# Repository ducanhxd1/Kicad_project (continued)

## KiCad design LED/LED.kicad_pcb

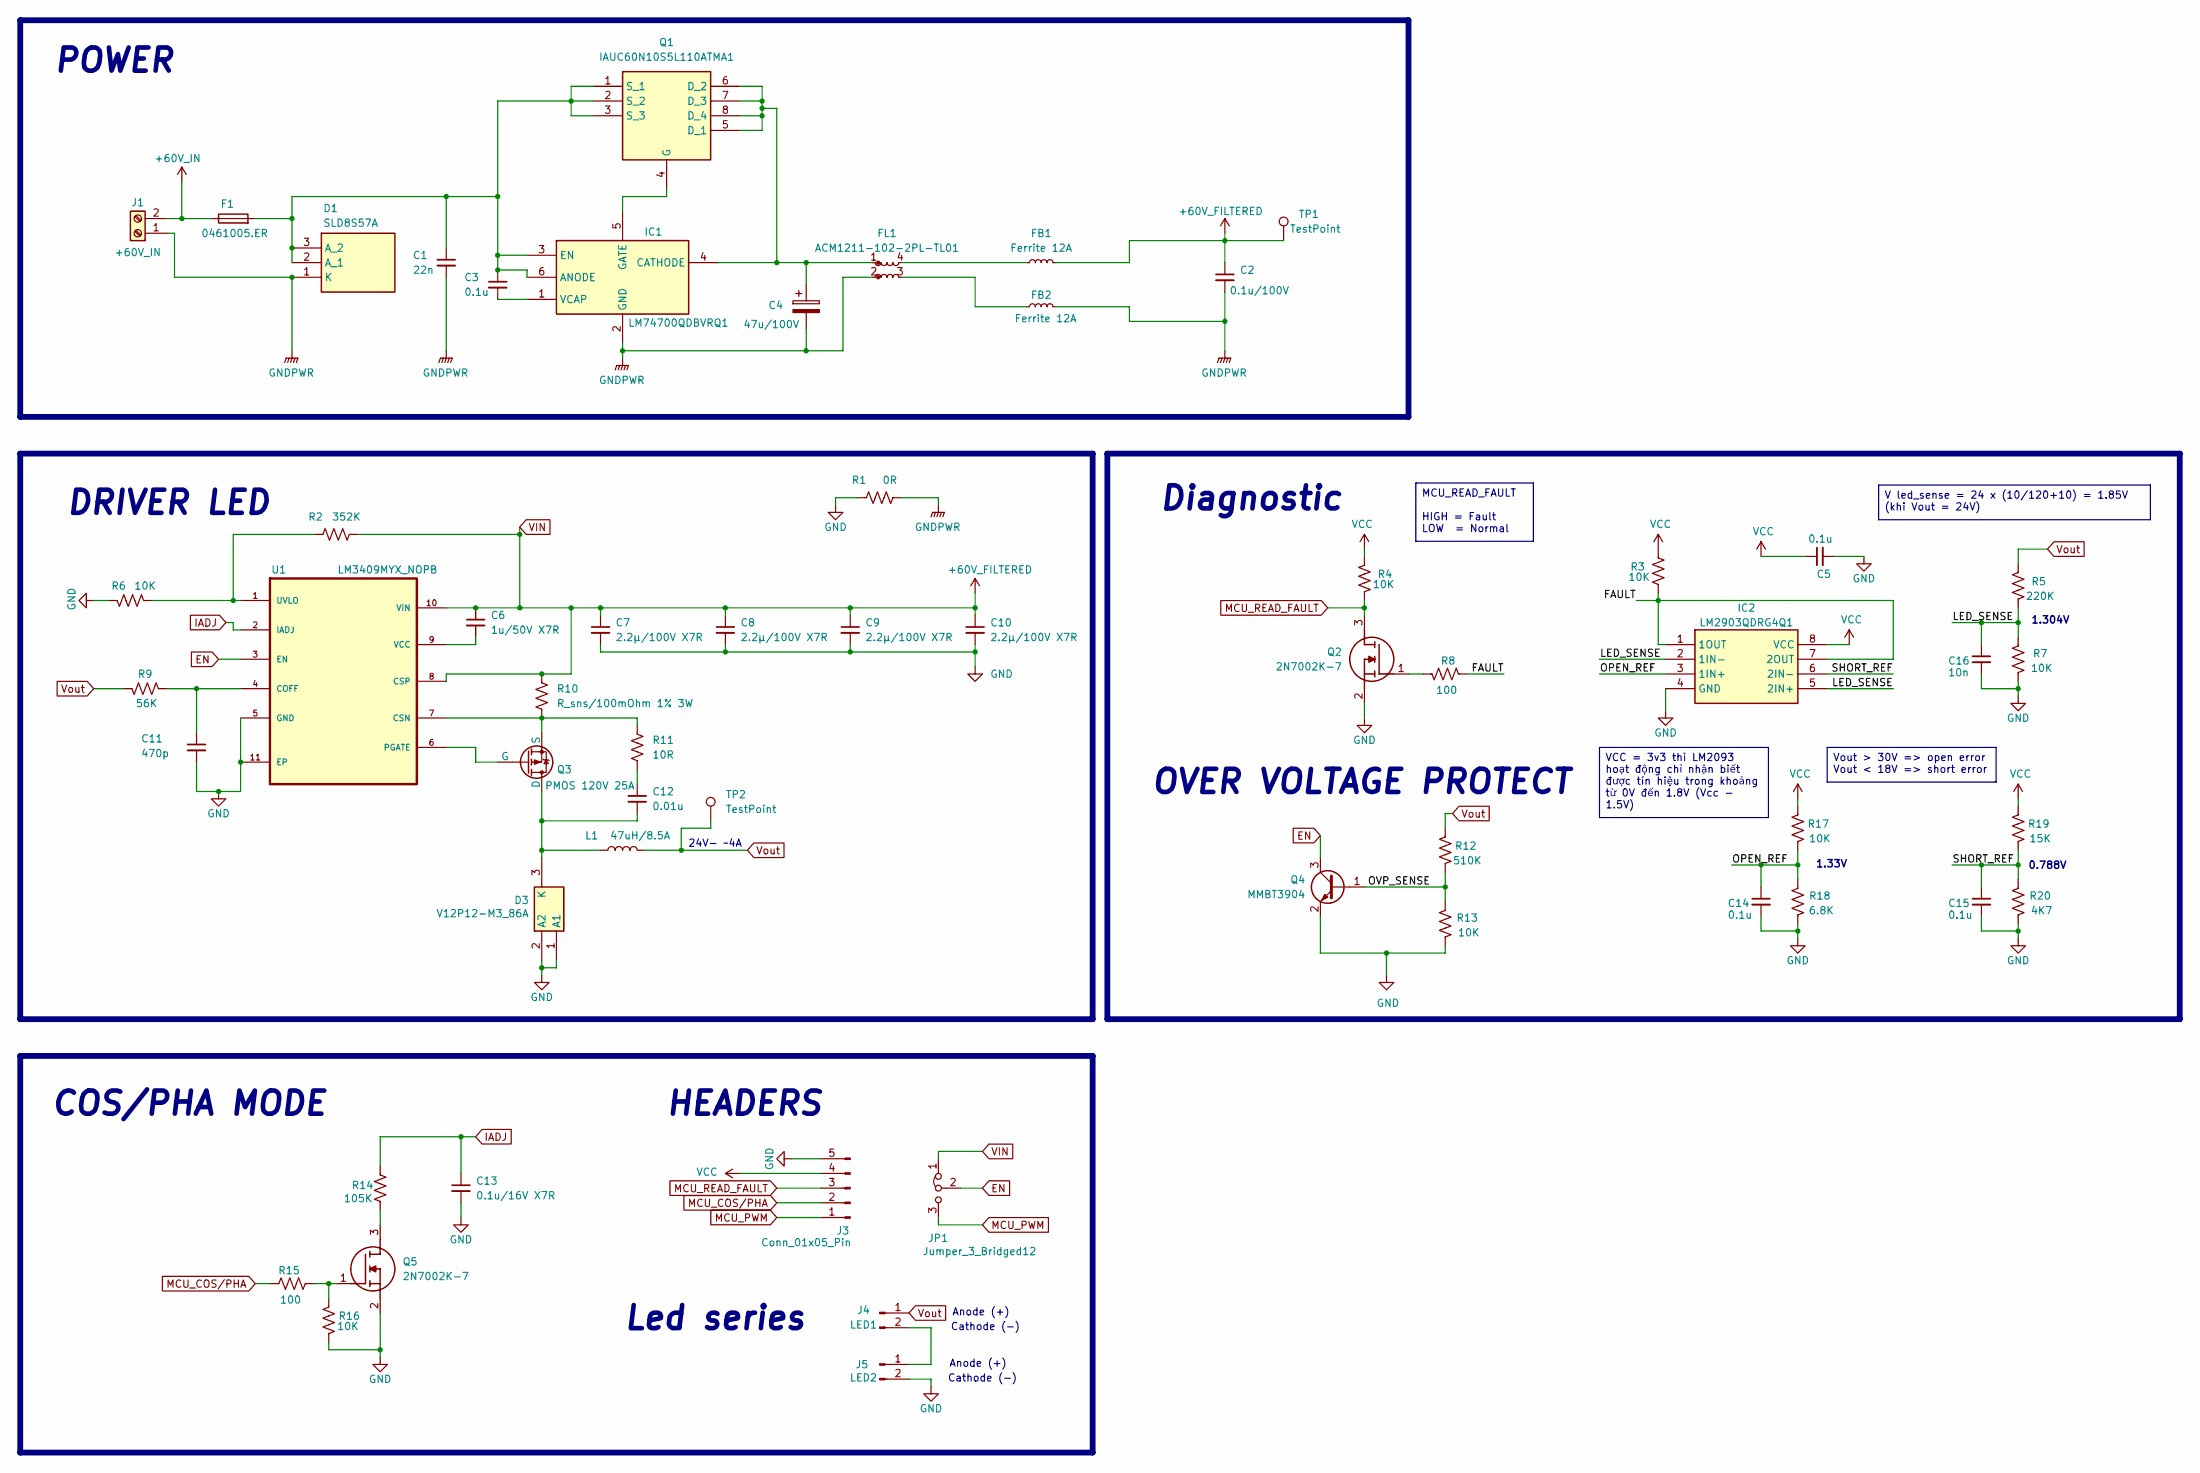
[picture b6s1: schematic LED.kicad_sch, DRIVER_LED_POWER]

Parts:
C1: 22n; C_0603_1608Metric_Pad1.08x0.95mm_HandSolder
C2: 0.1u/100V; C_0603_1608Metric_Pad1.08x0.95mm_HandSolder
C3, C5, C14, C15: 0.1u; C_0603_1608Metric_Pad1.08x0.95mm_HandSolder
C4: 47u/100V; CP_Elec_10x10.5
C6: 1u/50V X7R; C_0603_1608Metric_Pad1.08x0.95mm_HandSolder
C7, C8, C9, C10: 2.2µ/100V X7R; C_0603_1608Metric_Pad1.08x0.95mm_HandSolder
C11: 470p; C_0603_1608Metric_Pad1.08x0.95mm_HandSolder
C12: 0.01u; C_0603_1608Metric_Pad1.08x0.95mm_HandSolder
C13: 0.1u/16V X7R; C_0603_1608Metric_Pad1.08x0.95mm_HandSolder
C16: 10n; C_0603_1608Metric_Pad1.08x0.95mm_HandSolder
D1: SLD8S57A; Mouser Part Number 576-SLD8S57A
D3: V12P12-M3_86A; V12P12M386A; Manufacturer_Part_Number V12P12-M3/86A
F1: 0461005.ER; FUSC10131X312N
FB1, FB2: Ferrite 12A; BEADC3216X110N
FL1: ACM1211-102-2PL-TL01; ACM1211
IC1: LM74700QDBVRQ1; SOT95P280X145-6N; Mouser Part Number 595-LM74700QDBVRQ1
IC2: LM2903QDRG4Q1; SOIC127P600X175-8N; Mouser Part Number 595-LM2903QDRG4Q1
J1: +60V_IN; PinHeader_1x02_P2.54mm_Vertical
J3: Conn_01x05_Pin; JST_XH_B5B-XH-A_1x05_P2.50mm_Vertical
J4: LED1; JST_XH_B2B-XH-A_1x02_P2.50mm_Vertical
J5: LED2; JST_XH_B2B-XH-A_1x02_P2.50mm_Vertical
JP1: Jumper_3_Bridged12; PinHeader_1x03_P1.27mm_Vertical
L1: 47uH/8.5A; XAL1010
Q1: IAUC60N10S5L110ATMA1; Manufacturer_Part_Number IAUC60N10S5L110ATMA1
Q2, Q5: 2N7002K-7; SOT96P240X115-3N; Mouser Part Number 621-2N7002K-7
Q3: PMOS 120V 25A; SQD50P0825L_GE3
Q4: MMBT3904; SOT-23
R1: 0R; R_1206_3216Metric_Pad1.30x1.75mm_HandSolder
R2: 352K; R_0603_1608Metric_Pad0.98x0.95mm_HandSolder
R3, R4, R6, R7, R13, R16, R17: 10K; R_0603_1608Metric_Pad0.98x0.95mm_HandSolder
R5: 220K; R_0603_1608Metric_Pad0.98x0.95mm_HandSolder
R8, R15: 100; R_0603_1608Metric_Pad0.98x0.95mm_HandSolder
R9: 56K; R_0603_1608Metric_Pad0.98x0.95mm_HandSolder
R10: R_sns/100mOhm 1% 3W; R_2512_6332Metric_Pad1.40x3.35mm_HandSolder
R11: 10R; R_0603_1608Metric_Pad0.98x0.95mm_HandSolder
R12: 510K; R_0603_1608Metric_Pad0.98x0.95mm_HandSolder
R14: 105K; R_0603_1608Metric_Pad0.98x0.95mm_HandSolder
R18: 6.8K; R_0603_1608Metric_Pad0.98x0.95mm_HandSolder
R19: 15K; R_0603_1608Metric_Pad0.98x0.95mm_HandSolder
R20: 4K7; R_0603_1608Metric_Pad0.98x0.95mm_HandSolder
TP1, TP2: TestPoint; TestPoint_Pad_D1.0mm
U1: LM3409MYX_NOPB; IC_XTR111AIDGQR

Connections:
+60V_IN: F1.1, J1.2
/CS-: Q3.3 (S), R10.2, R11.1, U1.7 (CSN)
/FAULT: IC2.1 (1OUT), IC2.7 (2OUT), R3.1, R8.2
/LED_SENSE: C16.1, IC2.2 (1IN-), IC2.5 (2IN+), R5.1, R7.2
/OPEN_REF: C14.1, IC2.3 (1IN+), R17.1, R18.2
/OVP_SENSE: Q4.1 (B), R12.1, R13.2
/SHORT_REF: C15.1, IC2.6 (2IN-), R19.1, R20.2
EN: JP1.2 (C), Q4.3 (C), U1.3 (EN)
GND: C5.2, C7.2, C8.2, C9.2, C10.2, C11.2, C13.2, C14.2, C15.2, C16.2, D3.1 (A1), D3.2 (A2), IC2.4 (GND), J3.5, J5.2, Q2.2 (S), Q4.2 (E), Q5.2 (S), R1.2, R6.2, R7.1, R13.1, R16.1, R18.1, R20.1, U1.5 (GND), U1.11 (EP), U1.12, U1.13, U1.14, U1.15, U1.16
GNDPWR: C1.2, C2.2, C4.2, D1.1 (K), FB2.2, FL1.2, IC1.2 (GND), J1.1, R1.1
IADJ: C13.1, R14.1, U1.2 (IADJ)
MCU_COS/PHA: J3.2, R15.2
MCU_PWM: J3.1, JP1.3 (B)
MCU_READ_FAULT: J3.3, Q2.3 (D), R4.1
unnamed: C12.1, R11.2
unnamed: C1.1, C3.1, D1.2 (A_1), D1.3 (A_2), F1.2, IC1.3 (EN), IC1.6 (ANODE), Q1.1 (S_1), Q1.2 (S_2), Q1.3 (S_3), Q1.10
unnamed: C12.2, D3.3 (K), L1.1, Q3.1 (D)
unnamed: FB1.1, FL1.4
unnamed: FB2.1, FL1.3
unnamed: C4.1, FL1.1, IC1.4 (CATHODE), Q1.5 (D_1), Q1.6 (D_2), Q1.7 (D_3), Q1.8 (D_4), Q1.9
unnamed: IC1.5 (GATE), Q1.4 (G)
unnamed: C3.2, IC1.1 (VCAP)
unnamed: J4.2, J5.1
unnamed: Q2.1 (G), R8.1
unnamed: Q3.2 (G), U1.6 (PGATE)
unnamed: Q5.3 (D), R14.2
unnamed: Q5.1 (G), R15.1, R16.2
unnamed: C11.1, R9.1, U1.4 (COFF)
unnamed: R2.2, R6.1, U1.1 (UVLO)
unnamed: C6.2, U1.9 (VCC)
VCC: C5.1, IC2.8 (VCC), J3.4, R3.2, R4.2, R17.2, R19.2
VIN: C2.1, C6.1, C7.1, C8.1, C9.1, C10.1, FB1.2, JP1.1 (A), R2.1, R10.1, TP1.1 (1_1), U1.8 (CSP), U1.10 (VIN)
Vout: J4.1, L1.2, R5.2, R9.2, R12.2, TP2.1 (1_1)

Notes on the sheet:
Led series
OVER VOLTAGE PROTECT
Anode (+)
0.788V
Cathode (-)
24V- ~4A
HEADERS
Diagnostic
POWER
1.304V
DRIVER LED
COS/PHA MODE
1.33V
MCU_READ_FAULT HIGH = Fault LOW = Normal
V led_sense = 24 x (10/120+10) = 1.85V (khi Vout = 24V)
VCC = 3v3 thì LM2093 hoạt động chỉ nhận biết được tín hiệu trong khoảng từ 0V đến 1.8V (Vcc - 1.5V)
Vout > 30V => open error Vout < 18V => short error

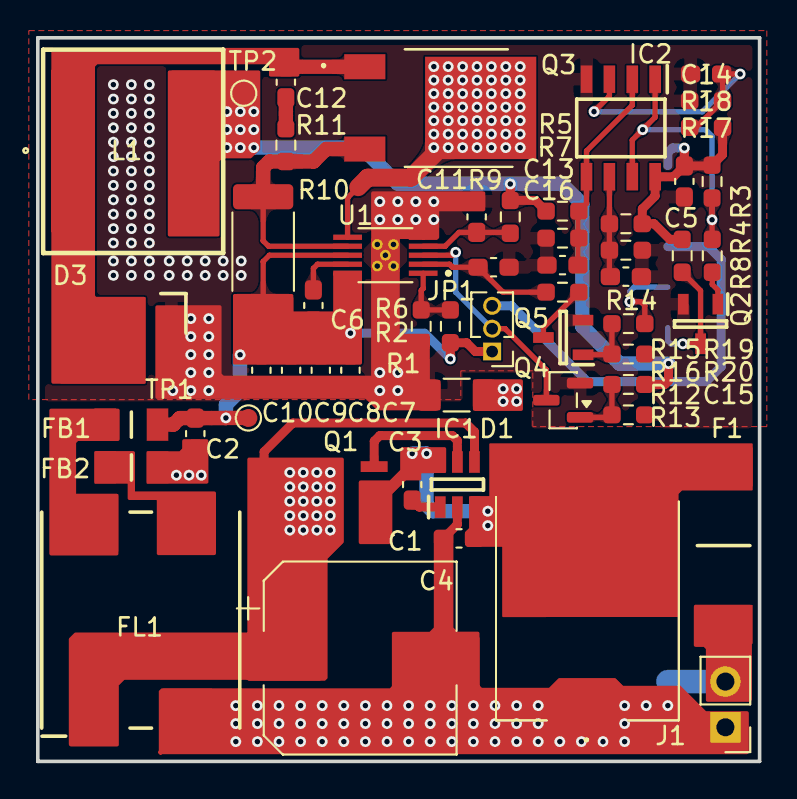
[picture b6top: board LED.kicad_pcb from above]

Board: 2 copper layers, 40.1 x 40.2 mm, 55 parts (0 on the bottom side), 30 nets.

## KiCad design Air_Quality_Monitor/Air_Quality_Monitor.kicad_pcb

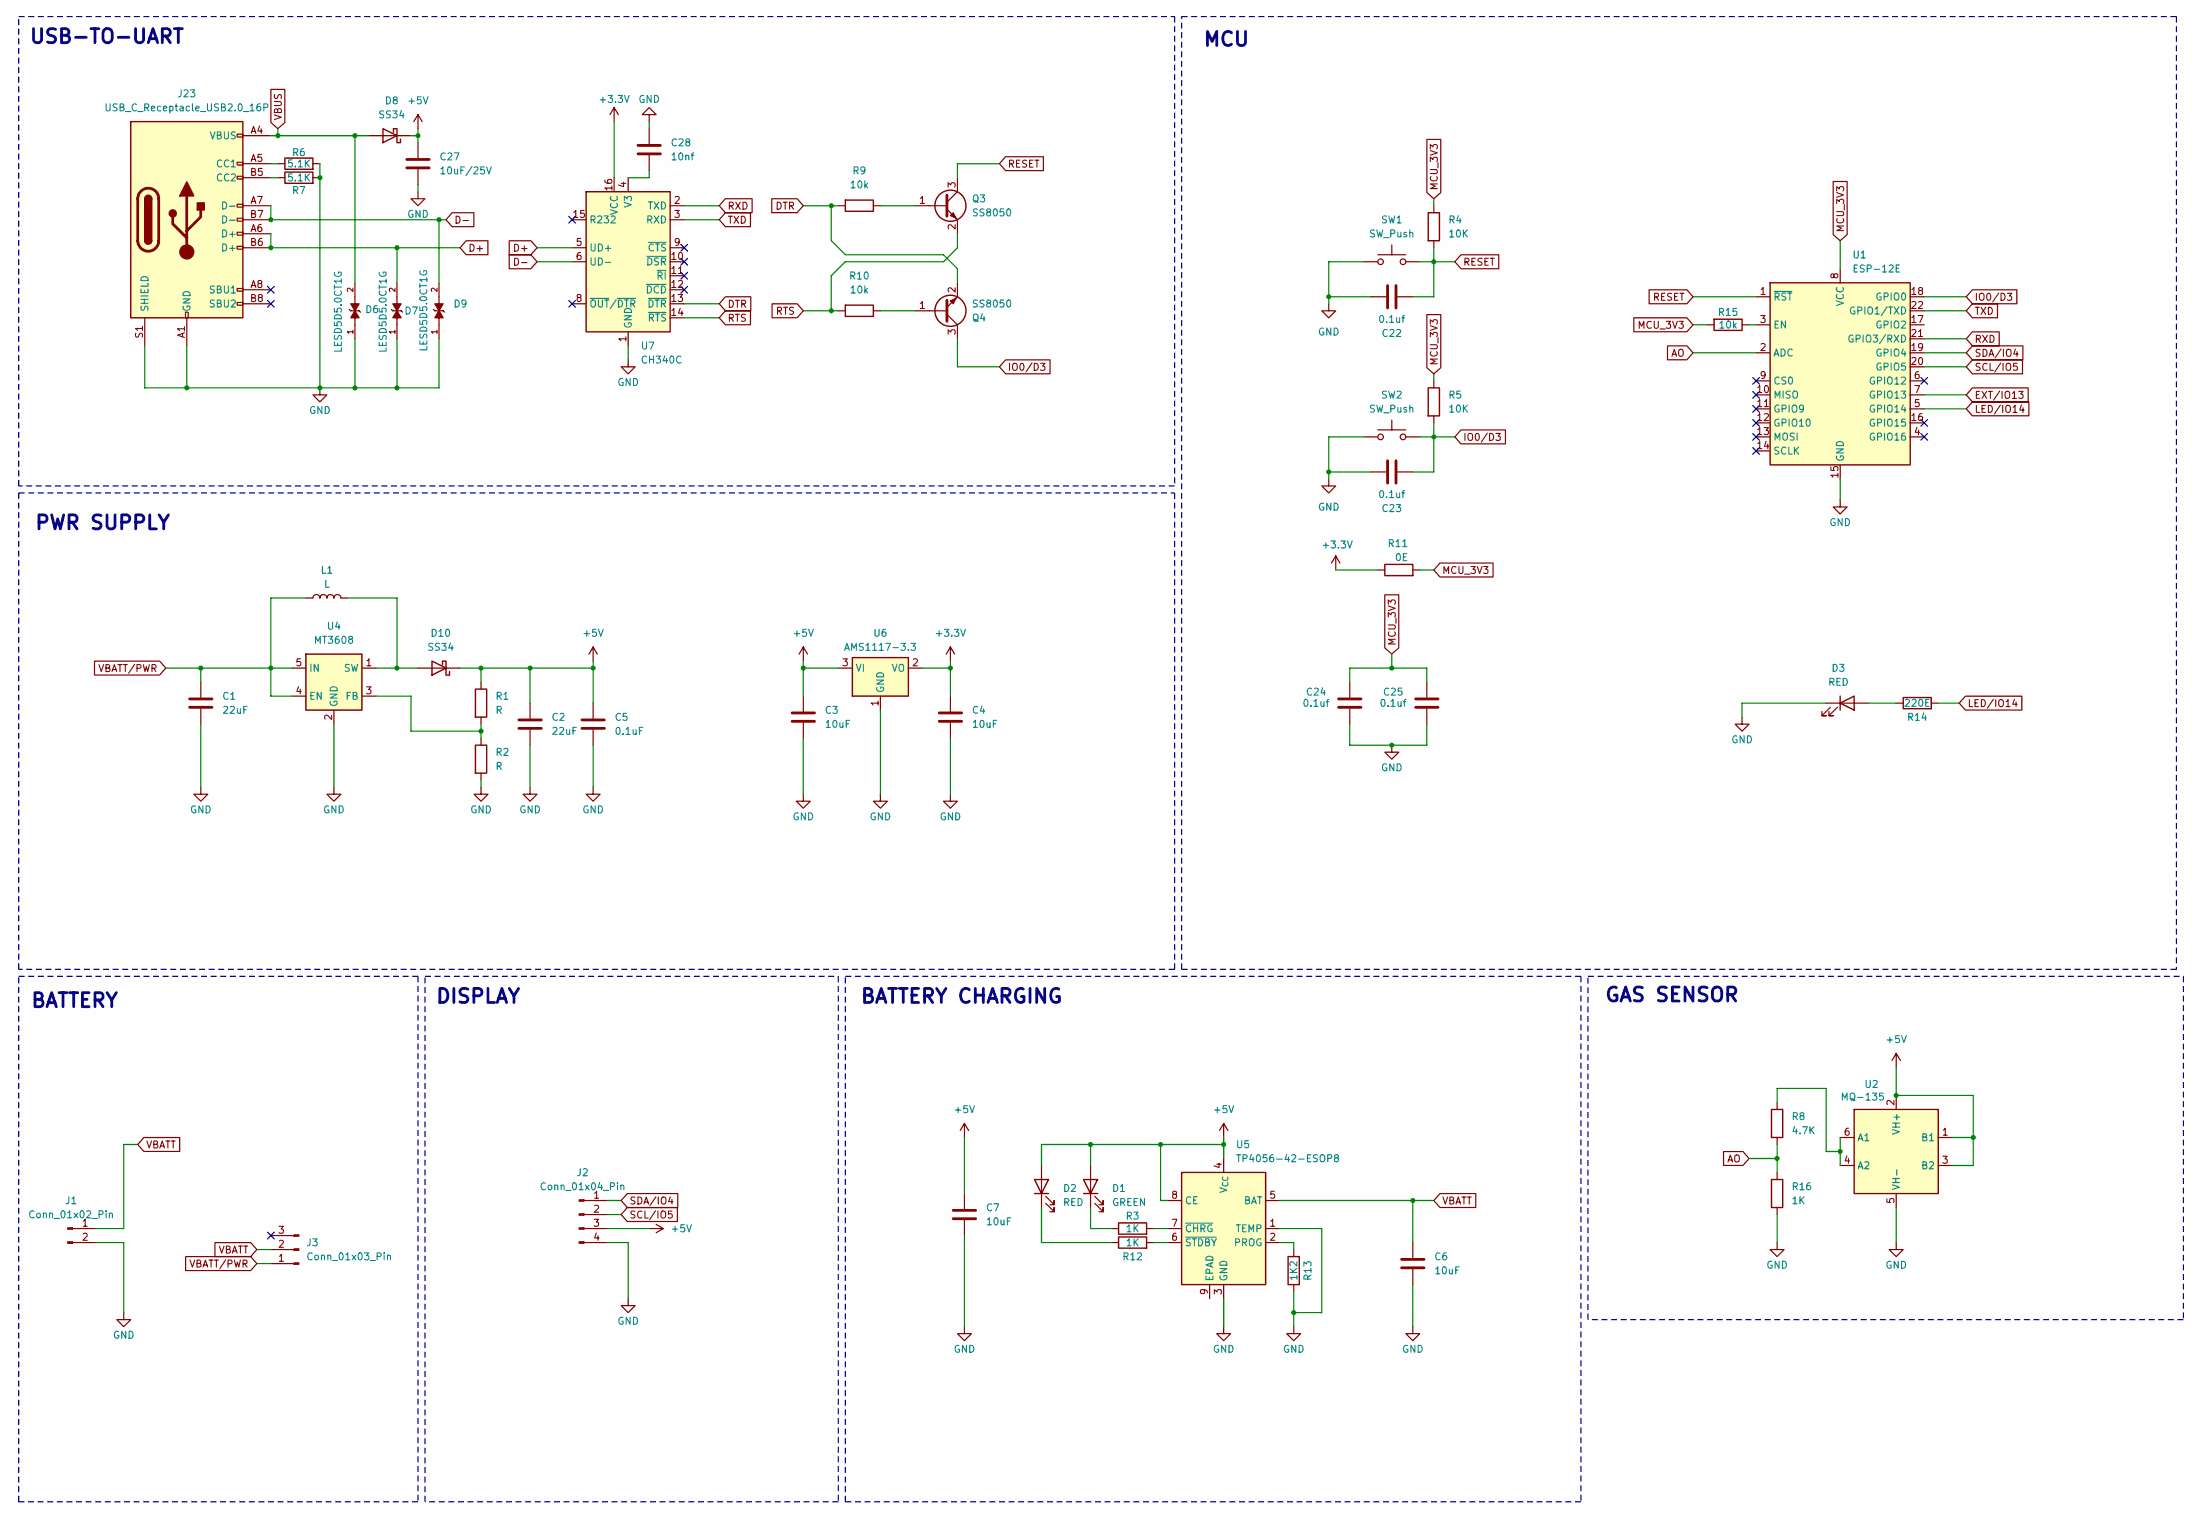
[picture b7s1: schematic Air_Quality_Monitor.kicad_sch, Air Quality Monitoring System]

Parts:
C1, C2: 22uF; C_1206_3216Metric
C3, C4, C6, C7: 10uF; C_1206_3216Metric
C5: 0.1uF; C_0603_1608Metric
C22, C23, C24, C25: 0.1uf; C_0603_1608Metric
C27: 10uF/25V; C_1206_3216Metric
C28: 10nf; C_0603_1608Metric
D1: GREEN; LED_0603_1608Metric
D2, D3: RED; LED_0603_1608Metric
D6, D7, D9: LESD5D5.0CT1G; TVS_LESD5D5.0CT1G; PARTREV O
D8, D10: SS34; D_SMA
J1: Conn_01x02_Pin; JST_PH_S2B-PH-K_1x02_P2.00mm_Horizontal
J2: Conn_01x04_Pin; PinSocket_1x04_P2.54mm_Vertical
J3: Conn_01x03_Pin; PinHeader_1x03_P2.54mm_Vertical
J23: USB_C_Receptacle_USB2.0_16P; USB_C_Receptacle_HCTL_HC-TYPE-C-16P-01A
L1: L; L_10.4x10.4_H4.8
Q3, Q4: SS8050; SOT-23
R1, R2: R; R_1206_3216Metric
R3, R12, R16: 1K; R_1206_3216Metric
R4, R5: 10K; R_1206_3216Metric
R6, R7: 5.1K; R_0603_1608Metric
R8: 4.7K; R_1206_3216Metric
R9, R10: 10k; R_0603_1608Metric
R11: 0E; R_0603_1608Metric
R13: 1K2; R_1206_3216Metric
R14: 220E; R_1206_3216Metric
R15: 10k; R_1206_3216Metric
SW1, SW2: SW_Push; SW_Push_SPST_NO_Alps_SKRK
U1: ESP-12E
U2: MQ-135; MQ-6
U4: MT3608; SOT-23-6
U5: TP4056-42-ESOP8; SOIC-8-1EP_3.9x4.9mm_P1.27mm_EP2.41x3.3mm_ThermalVias
U6: AMS1117-3.3; SOT-223-3_TabPin2
U7: CH340C; SOIC-16_3.9x9.9mm_P1.27mm

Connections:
+3.3V: C4.1, R11.1, U6.2 (VO), U7.16 (VCC)
+5V: C2.1, C3.1, C5.1, C7.1, C27.1, D1.2 (A), D2.2 (A), D8.1 (K), D10.1 (K), J2.3, R1.1, U2.1 (B1), U2.2 (VH+), U2.3 (B2), U5.4 (V_{CC}), U5.8 (CE), U6.3 (VI)
AO: R8.2, R16.1, U1.2 (ADC)
D+: D7.2, J23.A6 (D+), J23.B6 (D+), U7.5 (UD+)
D-: D9.2, J23.A7 (D-), J23.B7 (D-), U7.6 (UD-)
DTR: Q4.2 (E), R9.2, U7.13 (~DTR)
EXT/IO13: U1.7 (GPIO13)
GND: C1.2, C2.2, C3.2, C4.2, C5.2, C6.2, C7.2, C22.1, C23.1, C24.1, C25.1, C27.2, C28.1, D3.1 (K), D6.1, D7.1, D9.1, J1.2, J2.4, J23.A1 (GND), J23.A12 (GND), J23.B1 (GND), J23.B12 (GND), J23.S1 (SHIELD), R2.2, R6.2, R7.2, R13.1, R16.2, SW1.1, SW2.1, U1.15 (GND), U2.5 (VH-), U4.2 (GND), U5.1 (TEMP), U5.3 (GND), U6.1 (GND), U7.1 (GND)
IO0/D3: C23.2, Q4.3 (C), R5.2, SW2.2, U1.18 (GPIO0)
LED/IO14: R14.2, U1.5 (GPIO14)
MCU_3V3: C24.2, C25.2, R4.1, R5.1, R11.2, R15.2, U1.8 (VCC)
unnamed: D1.1 (K), R3.1
unnamed: D2.1 (K), R12.1
unnamed: D3.2 (A), R14.1
unnamed: D10.2 (A), L1.2, U4.1 (SW)
unnamed: J23.A5 (CC1), R6.1
unnamed: J23.B5 (CC2), R7.1
unnamed: Q3.1 (B), R9.1
unnamed: Q4.1 (B), R10.1
unnamed: R15.1, U1.3 (EN)
unnamed: R8.1, U2.4 (A2), U2.6 (A1)
unnamed: R1.2, R2.1, U4.3 (FB)
unnamed: R13.2, U5.2 (PROG)
unnamed: R3.2, U5.7 (~CHRG)
unnamed: R12.2, U5.6 (~STDBY)
unnamed: C28.2, U7.4 (V3)
RESET: C22.2, Q3.3 (C), R4.2, SW1.2, U1.1 (~RST)
RTS: Q3.2 (E), R10.2, U7.14 (~RTS)
RXD: U1.21 (GPIO3/RXD), U7.2 (TXD)
SCL/IO5: J2.2, U1.20 (GPIO5)
SDA/IO4: J2.1, U1.19 (GPIO4)
TXD: U1.22 (GPIO1/TXD), U7.3 (RXD)
VBATT: C6.1, J1.1, J3.2, U5.5 (BAT)
VBATT/PWR: C1.1, J3.1, L1.1, U4.4 (EN), U4.5 (IN)
VBUS: D6.2, D8.2 (A), J23.A4 (VBUS), J23.A9 (VBUS), J23.B4 (VBUS), J23.B9 (VBUS)

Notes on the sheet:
PWR SUPPLY
USB-TO-UART
DISPLAY
GAS SENSOR
BATTERY CHARGING
MCU
BATTERY

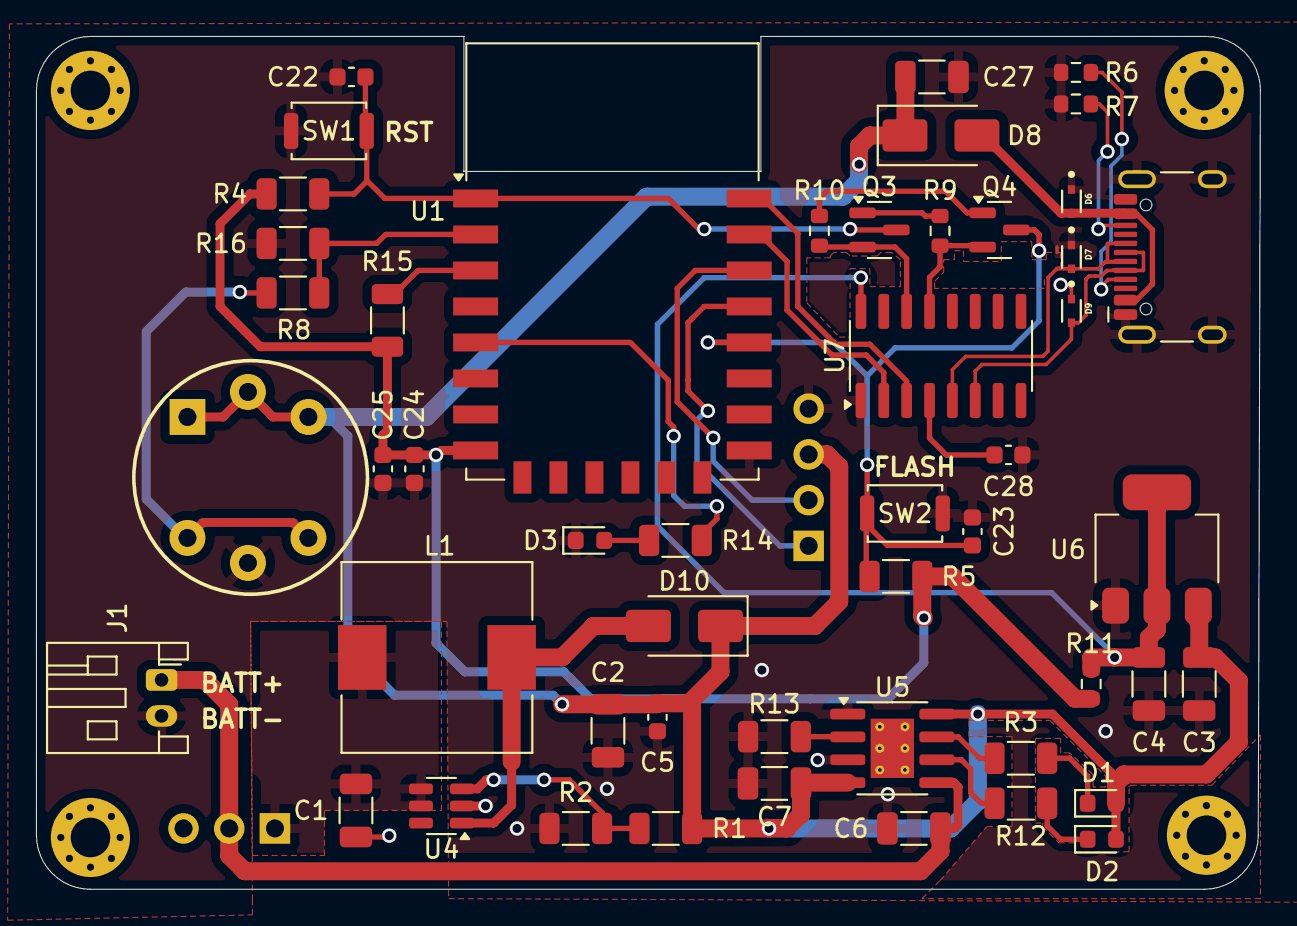
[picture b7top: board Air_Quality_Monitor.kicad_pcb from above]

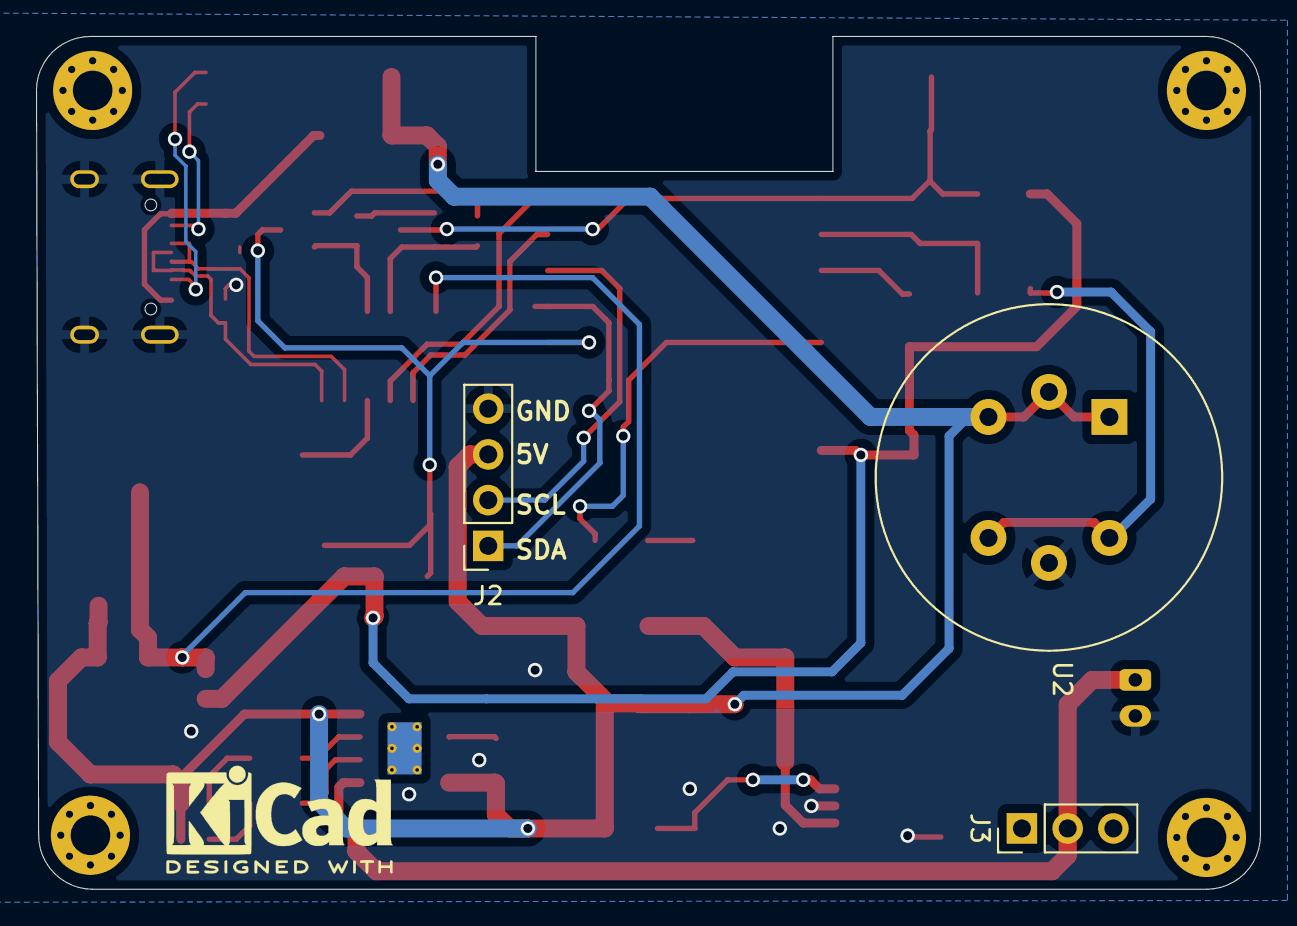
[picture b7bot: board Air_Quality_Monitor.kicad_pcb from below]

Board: 2 copper layers, 68.0 x 47.4 mm, 56 parts (3 on the bottom side), 34 nets.

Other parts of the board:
REFe: MountingHole_2.2mm_M2_Pad_Via
REFe#2, REFe#3, REFe#4: MountingHole_2.2mm_M2_Pad_Via

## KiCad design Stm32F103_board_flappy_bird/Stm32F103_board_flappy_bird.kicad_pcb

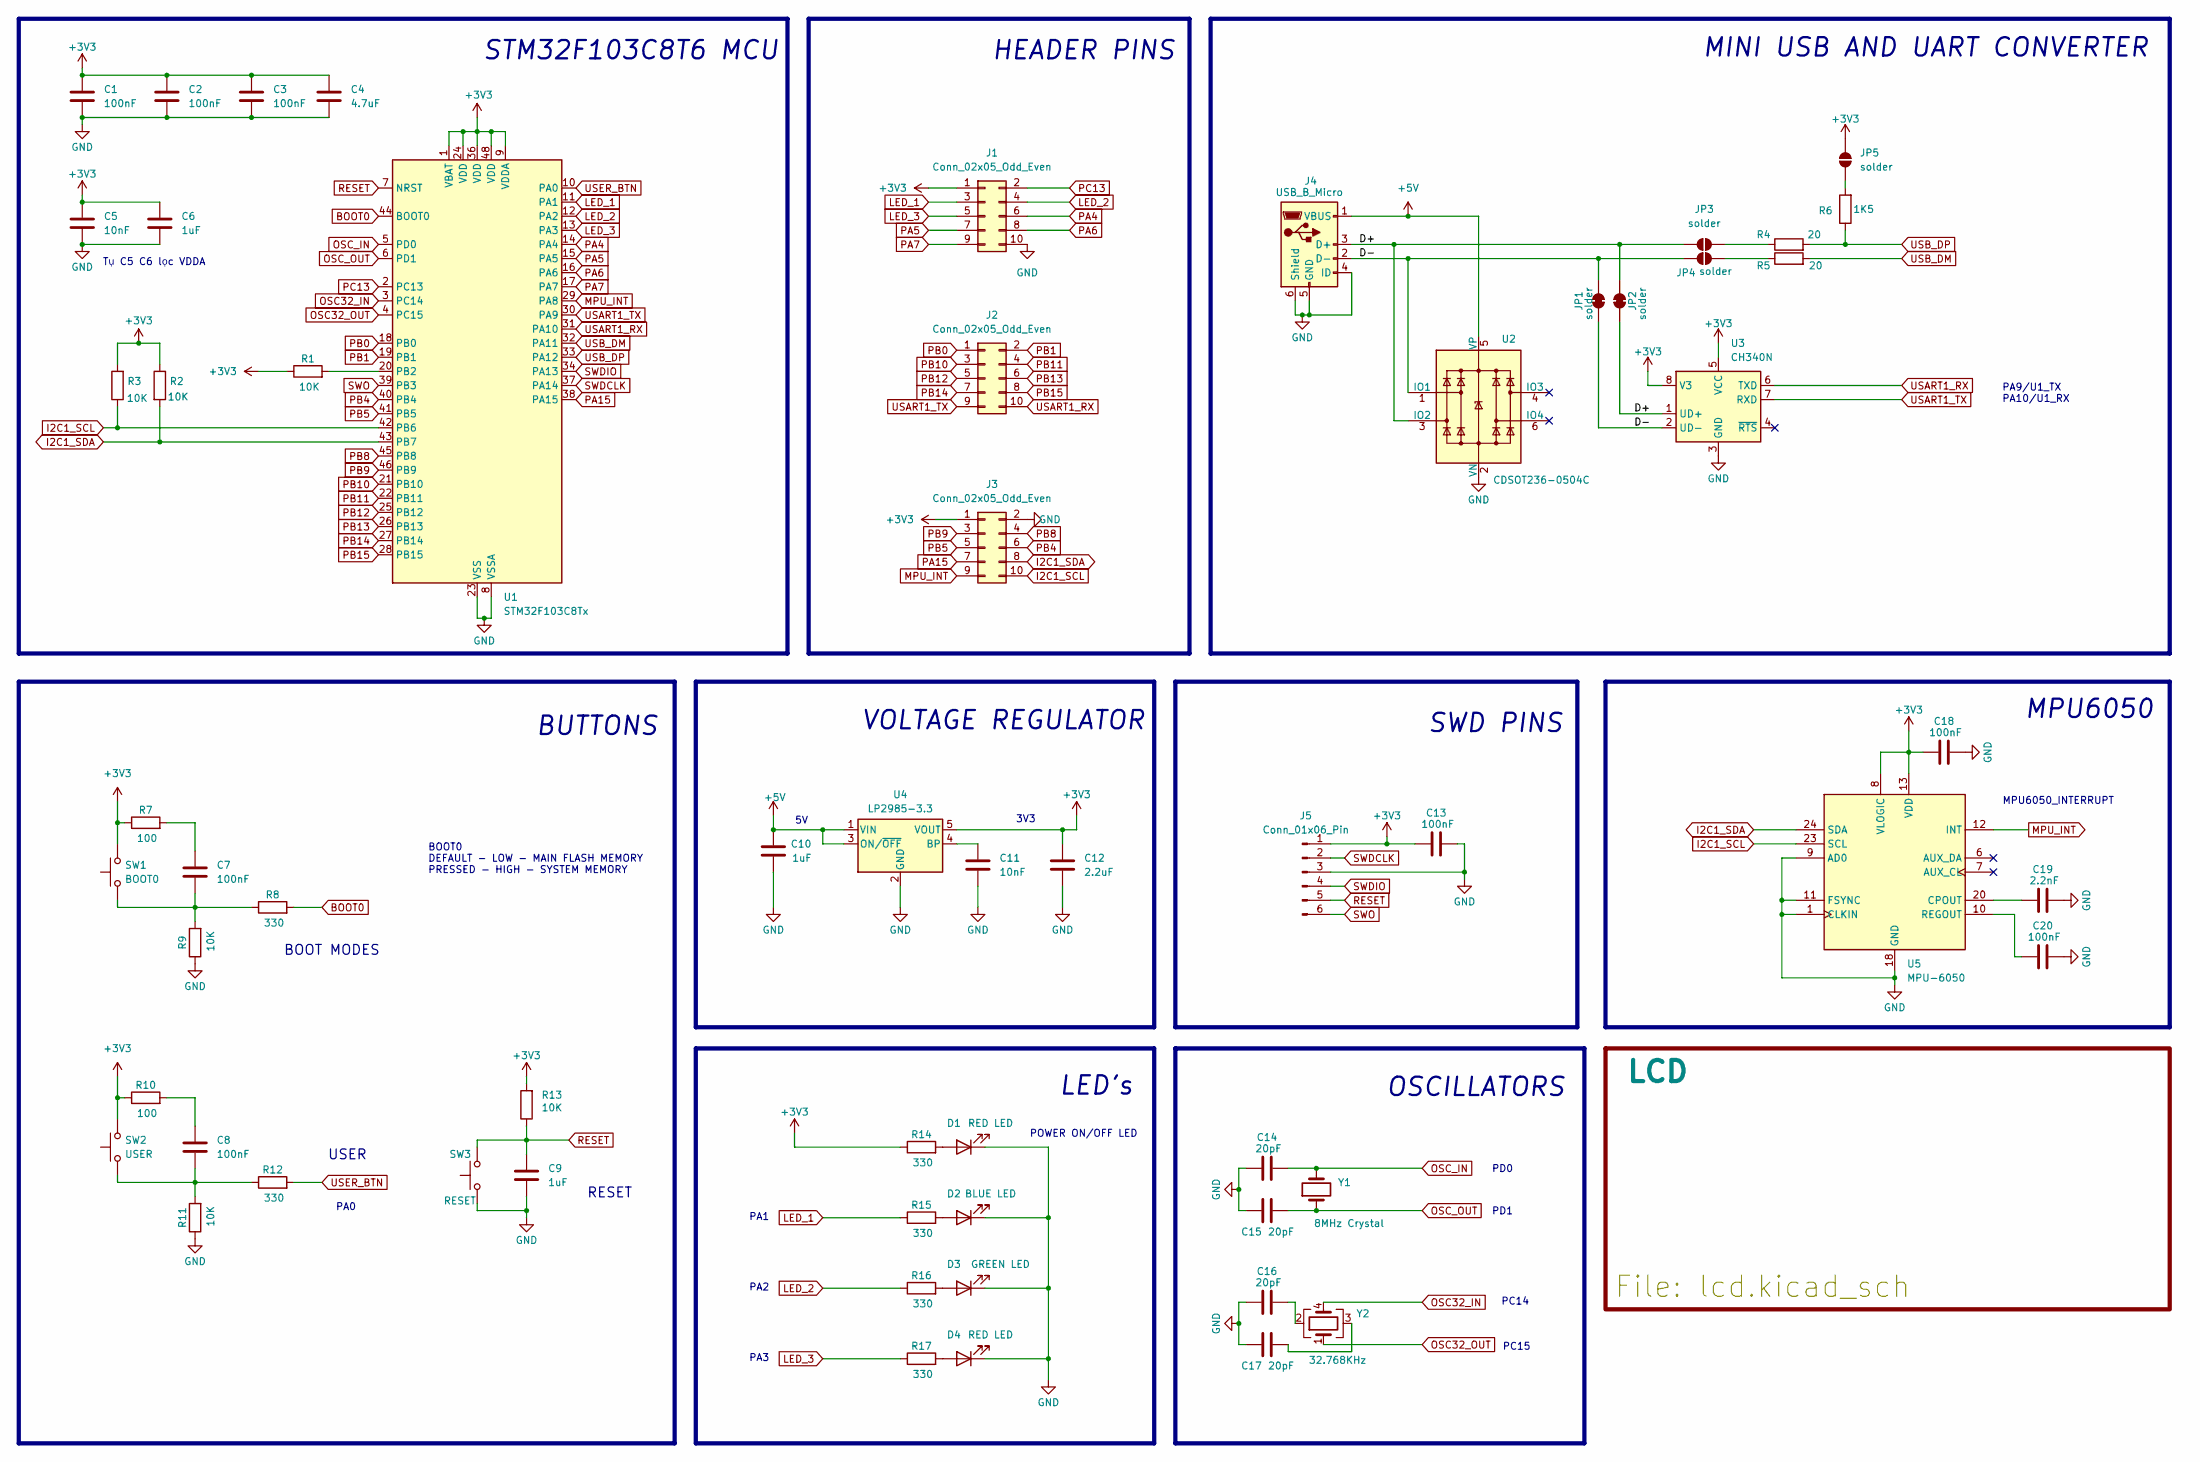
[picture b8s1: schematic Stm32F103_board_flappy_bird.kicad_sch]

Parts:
C1, C2, C3, C7, C8, C13, C18, C20: 100nF; C_0805_2012Metric_Pad1.18x1.45mm_HandSolder
C4: 4.7uF; C_0805_2012Metric_Pad1.18x1.45mm_HandSolder
C5, C11: 10nF; C_0805_2012Metric_Pad1.18x1.45mm_HandSolder
C6, C9, C10: 1uF; C_0805_2012Metric_Pad1.18x1.45mm_HandSolder
C12: 2.2uF; C_0805_2012Metric_Pad1.18x1.45mm_HandSolder
C14, C15, C16, C17: 20pF; C_0805_2012Metric_Pad1.18x1.45mm_HandSolder
C19: 2.2nF; C_0805_2012Metric_Pad1.18x1.45mm_HandSolder
D1, D4: RED LED; LED_0805_2012Metric_Pad1.15x1.40mm_HandSolder
D2: BLUE LED; LED_0805_2012Metric_Pad1.15x1.40mm_HandSolder
D3: GREEN LED; LED_0805_2012Metric_Pad1.15x1.40mm_HandSolder
J1, J2, J3: Conn_02x05_Odd_Even; PinSocket_2x05_P2.54mm_Vertical
J4: USB_B_Micro; USB_Micro-B_Molex-105017-0001
J5: Conn_01x06_Pin; PinSocket_1x06_P2.54mm_Horizontal
JP1, JP2: solder; SolderJumper-2_P1.3mm_Bridged2Bar_Pad1.0x1.5mm
JP3, JP4, JP5: solder; SolderJumper-2_P1.3mm_Open_Pad1.0x1.5mm
R1, R2, R3, R9, R11, R13: 10K; R_0805_2012Metric_Pad1.20x1.40mm_HandSolder
R4, R5: 20; R_0805_2012Metric_Pad1.20x1.40mm_HandSolder
R6: 1K5; R_0805_2012Metric_Pad1.20x1.40mm_HandSolder
R7, R10: 100; R_0805_2012Metric_Pad1.20x1.40mm_HandSolder
R8, R12, R14, R15, R16, R17: 330; R_0805_2012Metric_Pad1.20x1.40mm_HandSolder
SW1: BOOT0; SW_Tactile_SPST_NO_Straight_CK_PTS636Sx25SMTRLFS
SW2: USER; SW_Tactile_SPST_NO_Straight_CK_PTS636Sx25SMTRLFS
SW3: RESET; SW_Tactile_SPST_NO_Straight_CK_PTS636Sx25SMTRLFS
U1: STM32F103C8Tx; LQFP-48_7x7mm_P0.5mm
U2: CDSOT236-0504C; SOT-23-6
U3: CH340N; JEITA_SOIC-8_3.9x4.9mm_P1.27mm
U4: LP2985-3.3; SOT-23-5
U5: MPU-6050; InvenSense_QFN-24_4x4mm_P0.5mm
Y1: 8MHz Crystal; Crystal_SMD_HC49-SD
Y2: 32.768KHz; Crystal_SMD_SeikoEpson_MC306-4Pin_8.0x3.2mm_HandSoldering

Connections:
+3V3: C1.1, C2.1, C3.1, C4.1, C5.1, C6.1, C12.1, C13.1, C18.1, J1.1, J3.1, J5.1, JP5.2 (B), R1.1, R2.1, R3.2, R7.1, R10.1, R13.2, R14.1, SW1.2, SW2.2, U1.1 (VBAT), U1.9 (VDDA), U1.24 (VDD), U1.36 (VDD), U1.48 (VDD), U3.5 (VCC), U3.8 (V3), U4.5 (VOUT), U5.8 (VLOGIC), U5.13 (VDD)
+5V: C10.1, J4.1 (VBUS), U2.5 (VP), U4.1 (VIN), U4.3 (ON/~OFF)
/D+: J4.3 (D+), JP2.1 (A), JP2.2 (B), JP3.1 (A), U2.3 (IO2), U3.1 (UD+)
/D-: J4.2 (D-), JP1.1 (A), JP1.2 (B), JP4.1 (A), U2.1 (IO1), U3.2 (UD-)
BOOT0: R8.2, U1.44 (BOOT0)
GND: C1.2, C2.2, C3.2, C4.2, C5.2, C6.2, C9.2, C10.2, C11.2, C12.2, C13.2, C14.1, C15.1, C16.1, C17.1, C18.2, C19.2, C20.2, D1.1 (K), D2.1 (K), D3.1 (K), D4.1 (K), J1.10, J3.2, J4.4 (ID), J4.5 (GND), J4.6 (Shield), J5.3, R9.1, R11.1, SW3.1, U1.8 (VSSA), U1.23 (VSS), U1.35 (VSS), U1.47 (VSS), U2.2 (VN), U3.3 (GND), U4.2 (GND), U5.1 (CLKIN), U5.9 (AD0), U5.11 (FSYNC), U5.18 (GND)
I2C1_SCL: J3.10, R3.1, U1.42 (PB6), U5.23 (SCL)
I2C1_SDA: J3.8, R2.2, U1.43 (PB7), U5.24 (SDA)
LED_1: J1.3, R15.1, U1.11 (PA1)
LED_2: J1.4, R16.1, U1.12 (PA2)
LED_3: J1.5, R17.1, U1.13 (PA3)
MPU_INT: J3.9, U1.29 (PA8), U5.12 (INT)
unnamed: C7.1, R7.2
unnamed: C7.2, R8.1, R9.2, SW1.1
unnamed: C8.1, R10.2
unnamed: C8.2, R11.2, R12.1, SW2.1
unnamed: C16.2, Y2.2
unnamed: C17.2, Y2.3
unnamed: D1.2 (A), R14.2
unnamed: D2.2 (A), R15.2
unnamed: D3.2 (A), R16.2
unnamed: D4.2 (A), R17.2
unnamed: JP3.2 (B), R4.1
unnamed: JP4.2 (B), R5.1
unnamed: JP5.1 (A), R6.2
unnamed: R1.2, U1.20 (PB2)
unnamed: C11.1, U4.4 (BP)
unnamed: C19.1, U5.20 (CPOUT)
unnamed: C20.1, U5.10 (REGOUT)
OSC32_IN: U1.3 (PC14), Y2.4
OSC32_OUT: U1.4 (PC15), Y2.1
OSC_IN: C14.2, U1.5 (PD0), Y1.2
OSC_OUT: C15.2, U1.6 (PD1), Y1.1
PA4: J1.6, U1.14 (PA4)
PA5: J1.7, U1.15 (PA5)
PA6: J1.8, U1.16 (PA6)
PA7: J1.9, U1.17 (PA7)
PA15: J3.7, U1.38 (PA15)
PB0: J2.1, U1.18 (PB0)
PB1: J2.2, U1.19 (PB1)
PB4: J3.6, U1.40 (PB4)
PB5: J3.5, U1.41 (PB5)
PB8: J3.4, U1.45 (PB8)
PB9: J3.3, U1.46 (PB9)
PB10: J2.3, U1.21 (PB10)
PB11: J2.4, U1.22 (PB11)
PB12: J2.5, U1.25 (PB12)
PB13: J2.6, U1.26 (PB13)
PB14: J2.7, U1.27 (PB14)
PB15: J2.8, U1.28 (PB15)
PC13: J1.2, U1.2 (PC13)
RESET: C9.1, J5.5, R13.1, SW3.2, U1.7 (NRST)
SWDCLK: J5.2, U1.37 (PA14)
SWDIO: J5.4, U1.34 (PA13)
SWO: J5.6, U1.39 (PB3)
USART1_RX: J2.10, U1.31 (PA10), U3.6 (TXD)
USART1_TX: J2.9, U1.30 (PA9), U3.7 (RXD)
USB_DM: R5.2, U1.32 (PA11)
USB_DP: R4.2, R6.1, U1.33 (PA12)
USER_BTN: R12.2, U1.10 (PA0)

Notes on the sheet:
PA9/U1_TX PA10/U1_RX
USER
OSCILLATORS
VOLTAGE REGULATOR
PA3
BUTTONS
HEADER PINS
BOOT MODES
POWER ON/OFF LED
PD1
MINI USB AND UART CONVERTER
MPU6050_INTERRUPT
LED's
PA1
RESET
MPU6050
PA0
STM32F103C8T6 MCU
3V3
PD0
SWD PINS
PC15
PC14
BOOT0 DEFAULT - LOW - MAIN FLASH MEMORY PRESSED - HIGH - SYSTEM MEMORY
PA2
Tụ C5 C6 lọc VDDA

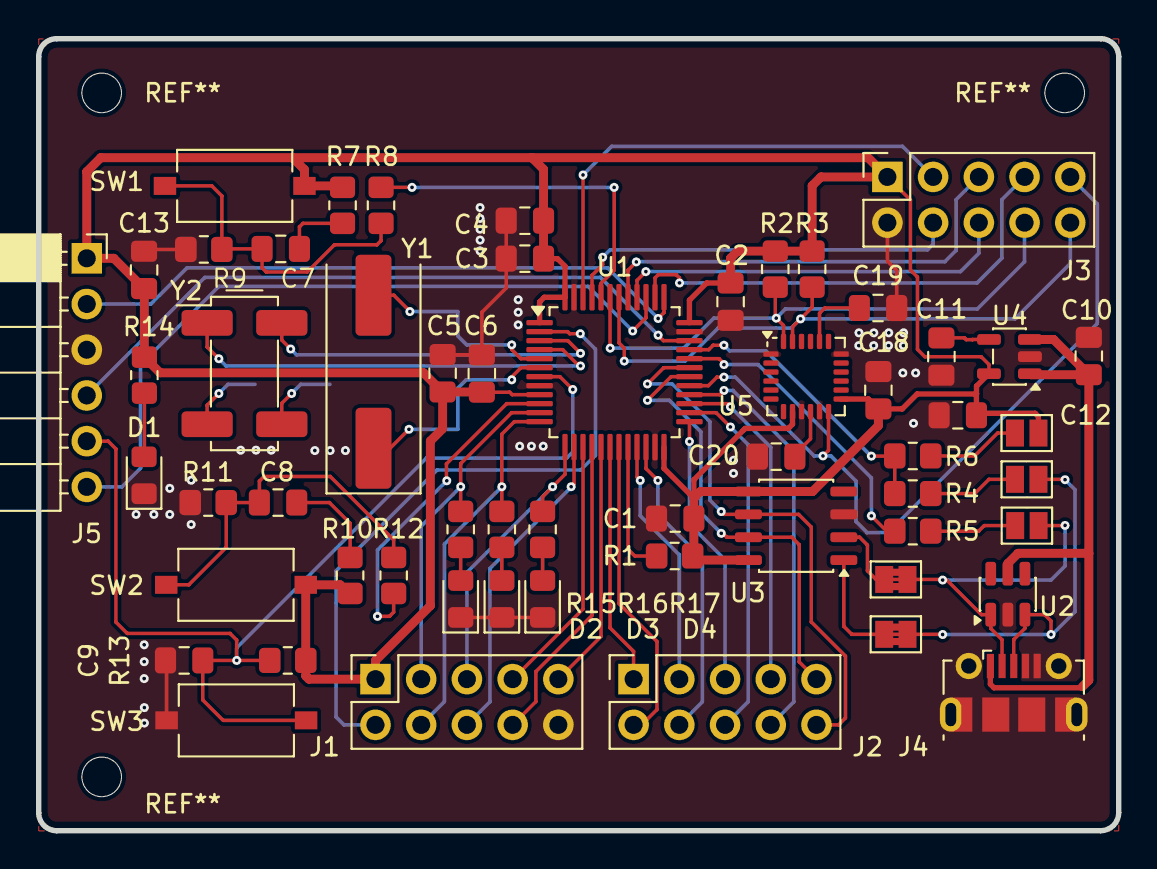
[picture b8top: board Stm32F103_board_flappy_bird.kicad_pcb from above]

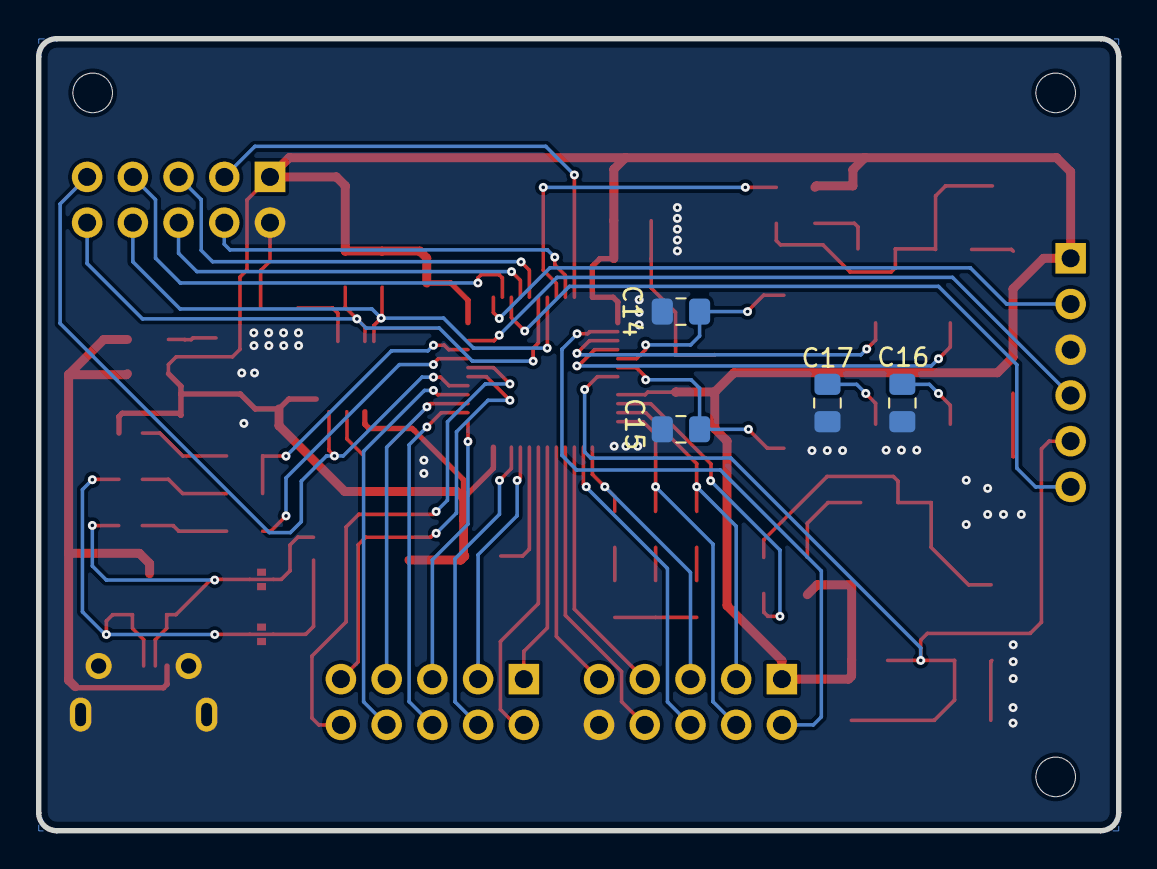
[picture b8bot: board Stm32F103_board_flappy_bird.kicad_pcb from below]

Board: 2 copper layers, 60.0 x 44.0 mm, 61 parts (4 on the bottom side), 60 nets.

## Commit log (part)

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2025-12-02 project stm32f103 mpu6050 lcd spi gc9a01a
2026-03-27 project esp-12E practice
2026-04-08 add schematic_practice kicad
2026-04-09 layout 2-layers done!
2026-04-10 add TOP & BOTTM image
2026-04-28 add vias Gnd
2026-04-28 update new image board top&bottom
2026-06-13 board Driver Led Power design by DucAnh
2026-06-22 board Driver Led Power completed!
